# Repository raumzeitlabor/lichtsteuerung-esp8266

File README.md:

ESP8266 Addon-Board für Lichtsteuerung

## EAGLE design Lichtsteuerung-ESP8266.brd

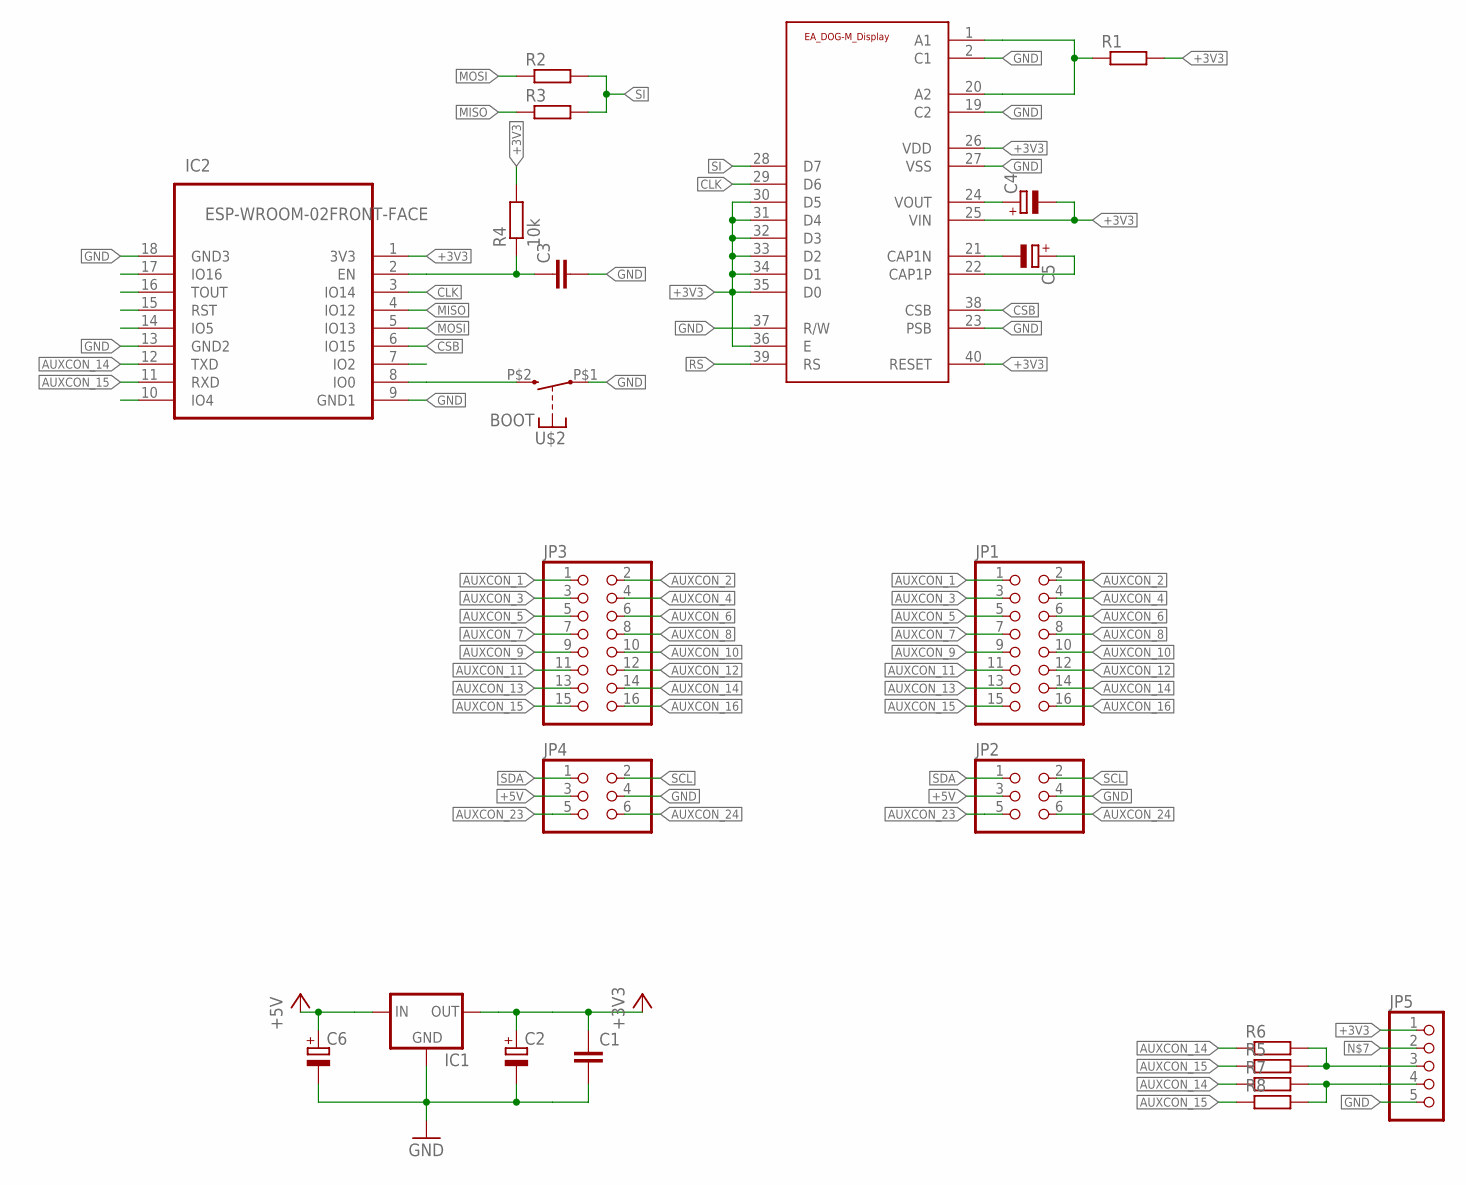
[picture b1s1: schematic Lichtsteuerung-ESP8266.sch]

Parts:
C1, C3: C-EUC1206; C1206
C2, C6: CPOL-EUC/6032-28R; C/6032-28R
C4, C5: CPOL-EUSMCA; SMC_A
IC1: LM1117; SOT223
IC2: ESP-WROOM-02FRONT-FACE; FRONT-FACE
JP1, JP3: PINHD-2X8; 2X08
JP2, JP4: PINHD-2X3; 2X03
JP5: PINHD-1X5; 1X05
R1, R2, R3, R5, R6, R7, R8: R-EU_R1206; R1206
R4: 10k; R1206
U$1: EA_DOG-M_DISPLAY; E_DOG-M_DISPLAY
U$2: BOOT; SKPM

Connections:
+3V3: C1.1, C2.+, C4.-, IC1.2 (OUT), IC2.1 (3V3), JP5.1, R1.2, R4.2, U$1.25 (VIN), U$1.26 (VDD), U$1.30 (D5), U$1.31 (D4), U$1.32 (D3), U$1.33 (D2), U$1.34 (D1), U$1.35 (D0), U$1.36 (E), U$1.40 (RESET)
+5V: C6.+, IC1.3 (IN), JP2.3, JP4.3
AUXCON_1: JP1.1, JP3.1
AUXCON_2: JP1.2, JP3.2
AUXCON_3: JP1.3, JP3.3
AUXCON_4: JP1.4, JP3.4
AUXCON_5: JP1.5, JP3.5
AUXCON_6: JP1.6, JP3.6
AUXCON_7: JP1.7, JP3.7
AUXCON_8: JP1.8, JP3.8
AUXCON_9: JP1.9, JP3.9
AUXCON_10: JP1.10, JP3.10
AUXCON_11: JP1.11, JP3.11
AUXCON_12: JP1.12, JP3.12
AUXCON_13: JP1.13, JP3.13
AUXCON_14: IC2.12 (TXD), JP1.14, JP3.14, R6.1, R7.1
AUXCON_15: IC2.11 (RXD), JP1.15, JP3.15, R5.1, R8.1
AUXCON_16: JP1.16, JP3.16
AUXCON_23: JP2.5, JP4.5
AUXCON_24: JP2.6, JP4.6
CLK: IC2.3 (IO14), U$1.29 (D6)
CSB: IC2.6 (IO15), U$1.38 (CSB)
GND: C1.2, C2.-, C3.2, C6.-, IC1.1 (GND), IC2.9 (GND1), IC2.13 (GND2), IC2.18 (GND3), JP2.4, JP4.4, JP5.5, U$1.2 (C1), U$1.19 (C2), U$1.23 (PSB), U$1.27 (VSS), U$1.37 (R/W), U$2.P$1
MISO: IC2.4 (IO12), R3.1
MOSI: IC2.5 (IO13), R2.1
unnamed: C4.+, U$1.24 (VOUT)
unnamed: R1.1, U$1.1 (A1), U$1.20 (A2)
unnamed: C5.-, U$1.21 (CAP1N)
unnamed: C3.1, IC2.2 (EN), R4.1
unnamed: IC2.8 (IO0), U$2.P$2 (S)
unnamed: C5.+, U$1.22 (CAP1P)
unnamed: JP5.3, R5.2, R6.2
unnamed: JP5.4, R7.2, R8.2
RS: U$1.39 (RS)
SCL: JP2.2, JP4.2
SDA: JP2.1, JP4.1
SI: R2.2, R3.2, U$1.28 (D7)

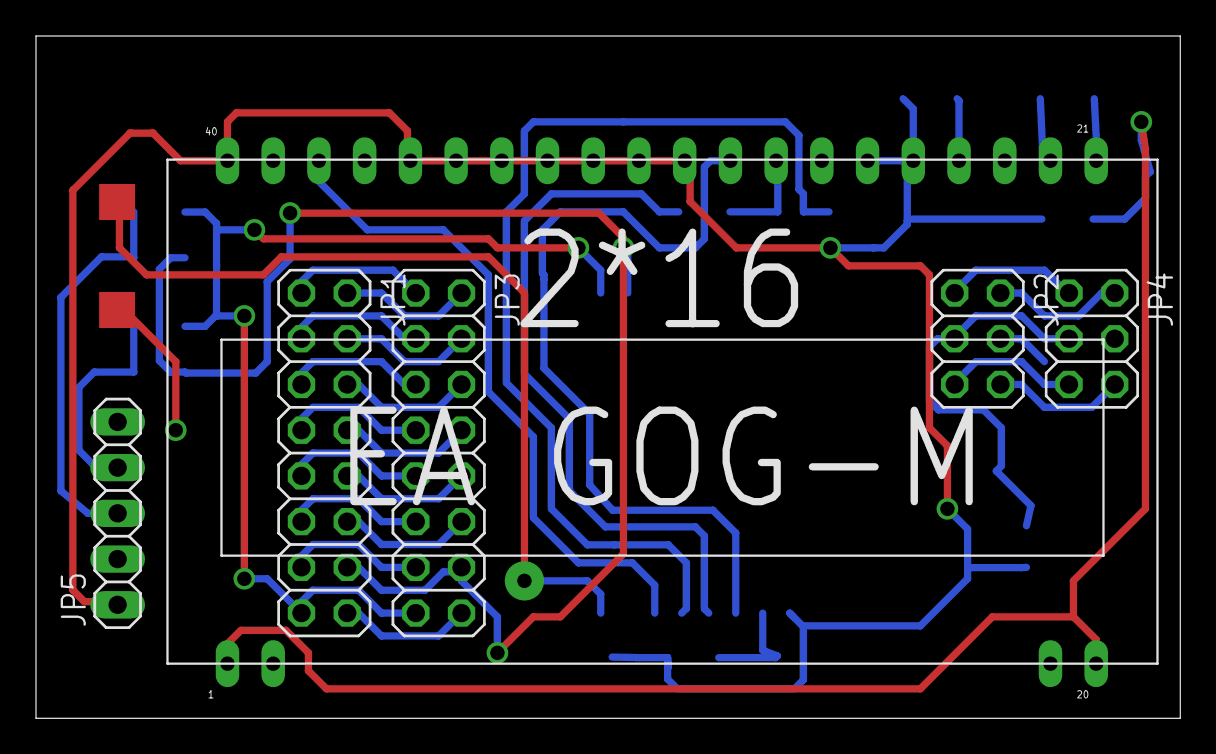
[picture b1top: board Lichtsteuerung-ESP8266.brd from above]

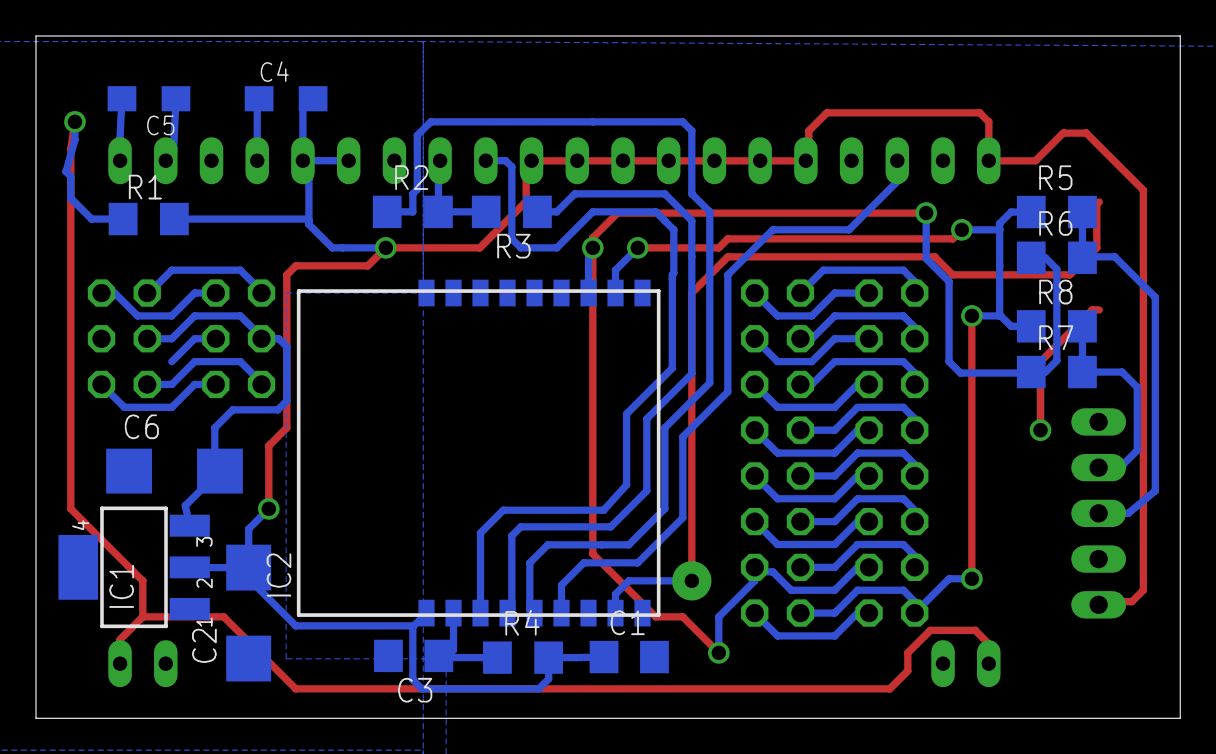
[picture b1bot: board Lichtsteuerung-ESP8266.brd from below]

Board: 2 copper layers, 63.6 x 37.9 mm, 23 parts (16 on the bottom side), 36 nets.
